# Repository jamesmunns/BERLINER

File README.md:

# BERLINER card/rack standard

BERLINER (BERLINER Euro Rack-Like Is Not Euro Rack) is an informal standard for USB and microcontroller oriented cards, using the eurorack form factor (but not the same power supply).

## The "standard"

Most of the "standard" here is the connector used on the boards. It's a 0.1" pitch 2x6 IDC connector. The picture above is taken looking at the BACK of the board.

The pins are:

| Use           | Pin   | Pin | Use             |
| :--           | :--   | --: | --:             |
| +20v power    | 1     |   2 |          Ground |
| +20v power    | 3     |   4 |          Ground |
| +5v0 power    | 5     |   6 |          Ground |
| +5v0 power    | 7     |   8 |          Ground |
| USB FS/HS D+  | 9     |  10 |    USB FS/HS D- |
| Ground        | 11    |  12 |          Common |

### "+20v power"

This is intended to be supplied by USB-PD, so it should be expected this rail can be any voltage 5v0 to 20v0 max. This rail is expected to have more wattage available than the +5v0 power rail. You may need a variable input DC/DC that can handle this.

### "+5v0 power"

This is a 5-volt-ish rail. Probably something in the tolerance of regular USB 5v, so +/- 0.25v. You can use this exclusively, but current may be shared with many other boards. If you need to do something high current, do it from the +20v power rail.

### "USB FS/HS D+/D-"

This is the normal differential pair used by USB Full Speed or USB High Speed.

### "Common"

This isn't super well defined, but it is intended as a low frequency, open-drain, interface, usable for clock sync or trigger. TBD who provides the pullup, maybe all boards on the order of 10k-50k (i.e. internal MCU pullups).

## `cards/` folder

These are board designs that are compatible with this "standard". They are intended to be mounted using the [Eurorack] device conventions, meaning a 128.5mm tall board, with M3 screws.

Some boards will have separate "face plates" or "covers" and "logic boards". In this case, the cover will be the full 128.5mm tall, and the logic board will often be a bit shorter (typ: 106.0mm), as it needs clearance to "drop into" the frame.

In these cases, covers will be mounted to the face plate either using hardware that is present (switches, dials), M3 headers, or some other mechanical means (outside the scope of this standard).

Feel free to open a PR with any designs you would like to share. KICAD designs preferred.

## `hubs/` folder

Since the cards don't take standard USB cables as input, it is generally necessary to have another PCBA that acts as an adapter. These have three main responsibilities:

1. Provide power to all boards, including the 20v0 rail and 5v0 rail
2. Provide data to all boards, often acting as a USB Hub
3. Provide 12-pin headers to connect to the cards, using an IDC ribbon cable

There are many options for chips that do this, but the CH334F (4 port USB hub) and CH224K (USB-PD negotiation) are used in some designs, and are available at reasonable prices.

Hubs can be present in two main forms:

1. As a "card", where the data and power ports face the front. See `hubs/usb-demo-4` for an example hub in this form factor.
2. As a "backplane", mounted somewhere inside the case, with connectors mounted somewhere on the case. See `hubs/backplane` for an example hub in this form factor, designed to fit the Sinusoda CAN eurorack case.

## License

idk something like cc-by-sa-nc?

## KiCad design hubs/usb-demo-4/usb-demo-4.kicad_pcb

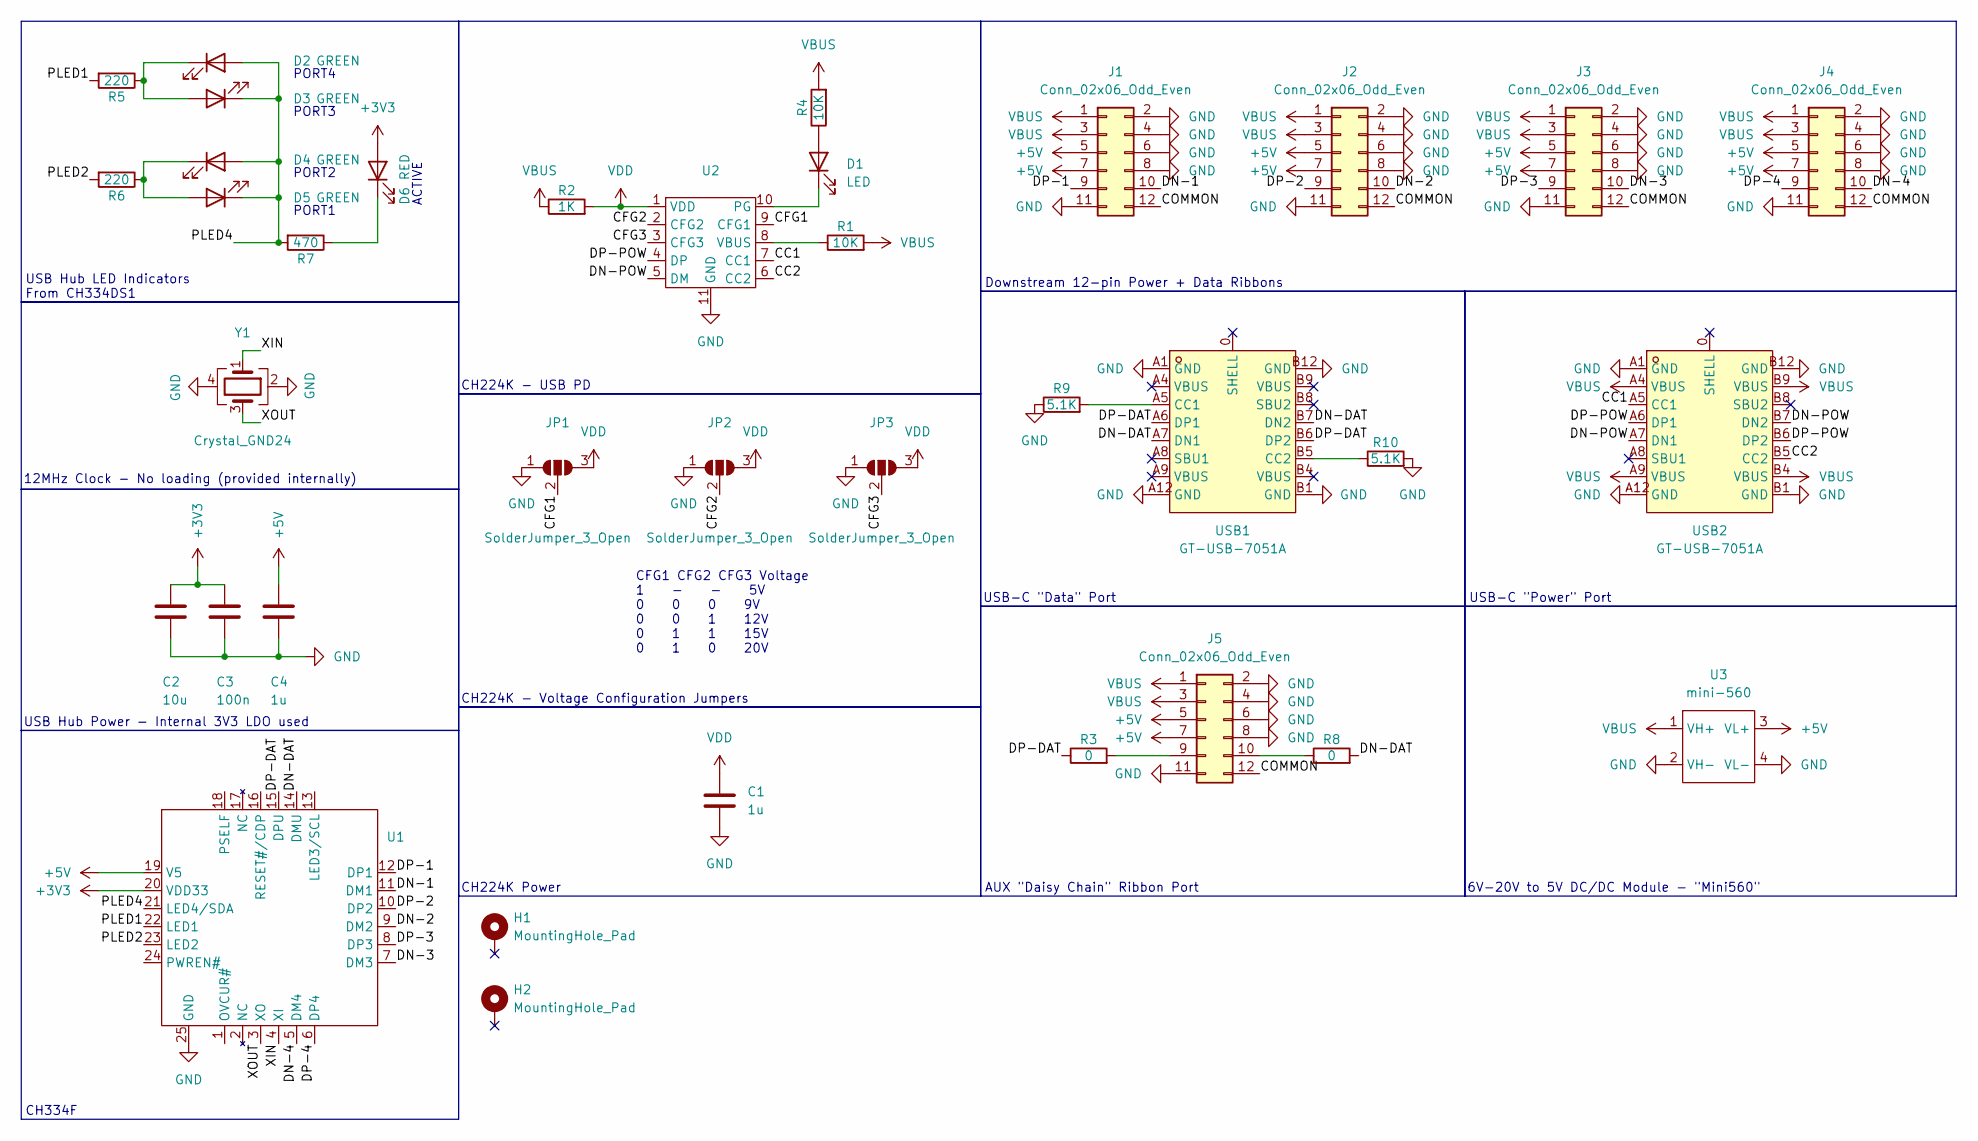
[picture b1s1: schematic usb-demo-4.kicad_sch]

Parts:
C1, C4: 1u; C_0603_1608Metric
C2: 10u; C_0603_1608Metric
C3: 100n; C_0603_1608Metric
D1: LED; D_0603_1608Metric
D2, D3, D4, D5: GREEN; D_0603_1608Metric
D6: RED; D_0603_1608Metric
H1, H2: MountingHole_Pad; MountingHole_3.2mm_M3_Pad_Via
J1, J2, J3, J4, J5: Conn_02x06_Odd_Even; PinHeader_2x06_P2.54mm_Vertical
JP1, JP2, JP3: SolderJumper_3_Open; SolderJumper-3_P2.0mm_Open_TrianglePad1.0x1.5mm
R1, R4: 10K; R_0603_1608Metric
R2: 1K; R_0603_1608Metric
R3, R8: 0; R_0603_1608Metric
R5, R6: 220; R_0603_1608Metric
R7: 470; R_0603_1608Metric
R9, R10: 5.1K; R_0603_1608Metric
U1: QFN-24-1EP_4x4mm_P0.5mm_EP2.7x2.7mm_ThermalVias
U2: ESSOP-10_L4.9-W3.9-P1.0-LS6.0-TL-EP
U3: mini-560; mini-560-smd
USB1, USB2: GT-USB-7051A; USB-C-SMD_GT-USB-7051A; LCSC Part C2843970
Y1: Crystal_GND24; Crystal_SMD_3225-4Pin_3.2x2.5mm

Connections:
+3V3: C2.1, C3.1, D6.2 (A), U1.20 (VDD33)
+5V: C4.1, J1.5, J1.7, J2.5, J2.7, J3.5, J3.7, J4.5, J4.7, J5.5, J5.7, U1.19 (V5), U3.3 (VL+)
/CC1: U2.7 (CC1), USB2.A5 (CC1)
/CC2: U2.6 (CC2), USB2.B5 (CC2)
/CFG1: JP1.2 (C), U2.9 (CFG1)
/CFG2: JP2.2 (C), U2.2 (CFG2)
/CFG3: JP3.2 (C), U2.3 (CFG3)
/COMMON: J1.12, J2.12, J3.12, J4.12, J5.12
/DN-1: J1.10, U1.11 (DM1)
/DN-2: J2.10, U1.9 (DM2)
/DN-3: J3.10, U1.7 (DM3)
/DN-4: J4.10, U1.5 (DM4)
/DN-DAT: R8.2, U1.14 (DMU), USB1.A7 (DN1), USB1.B7 (DN2)
/DN-POW: U2.5 (DM), USB2.A7 (DN1), USB2.B7 (DN2)
/DP-1: J1.9, U1.12 (DP1)
/DP-2: J2.9, U1.10 (DP2)
/DP-3: J3.9, U1.8 (DP3)
/DP-4: J4.9, U1.6 (DP4)
/DP-DAT: R3.1, U1.15 (DPU), USB1.A6 (DP1), USB1.B6 (DP2)
/DP-POW: U2.4 (DP), USB2.A6 (DP1), USB2.B6 (DP2)
/PLED1: R5.2, U1.22 (LED1)
/PLED2: R6.2, U1.23 (LED2)
/PLED4: D2.2 (A), D3.1 (K), D4.2 (A), D5.1 (K), R7.2, U1.21 (LED4/SDA)
/XIN: U1.4 (XI), Y1.1
/XOUT: U1.3 (XO), Y1.3
GND: C1.2, C2.2, C3.2, C4.2, J1.2, J1.4, J1.6, J1.8, J1.11, J2.2, J2.4, J2.6, J2.8, J2.11, J3.2, J3.4, J3.6, J3.8, J3.11, J4.2, J4.4, J4.6, J4.8, J4.11, J5.2, J5.4, J5.6, J5.8, J5.11, JP1.1 (A), JP2.1 (A), JP3.1 (A), R9.1, R10.2, U1.25 (GND), U2.11 (GND), U3.2 (VH-), U3.4 (VL-), USB1.A1 (GND), USB1.A12 (GND), USB1.B1 (GND), USB1.B12 (GND), USB2.A1 (GND), USB2.A12 (GND), USB2.B1 (GND), USB2.B12 (GND), Y1.2, Y1.4
unnamed: D1.2 (A), R4.1
unnamed: D1.1 (K), U2.10 (PG)
unnamed: D2.1 (K), D3.2 (A), R5.1
unnamed: D4.1 (K), D5.2 (A), R6.1
unnamed: D6.1 (K), R7.1
unnamed: J5.9, R3.2
unnamed: J5.10, R8.1
unnamed: R1.1, U2.8 (VBUS)
unnamed: R9.2, USB1.A5 (CC1)
unnamed: R10.1, USB1.B5 (CC2)
VBUS: J1.1, J1.3, J2.1, J2.3, J3.1, J3.3, J4.1, J4.3, J5.1, J5.3, R1.2, R2.1, R4.2, U3.1 (VH+), USB2.A4 (VBUS), USB2.A9 (VBUS), USB2.B4 (VBUS), USB2.B9 (VBUS)
VDD: C1.1, JP1.3 (B), JP2.3 (B), JP3.3 (B), R2.2, U2.1 (VDD)

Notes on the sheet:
CH224K - Voltage Configuration Jumpers
USB-C "Data" Port
AUX "Daisy Chain" Ribbon Port
USB Hub LED Indicators From CH334DS1
CFG1 CFG2 CFG3 Voltage 1 - - 5V 0 0 0 9V 0 0 1 12V 0 1 1 15V 0 1 0 20V
Downstream 12-pin Power + Data Ribbons
USB-C "Power" Port
PORT1
PORT2
ACTIVE
PORT4
CH334F
12MHz Clock - No loading (provided internally)
CH224K Power
6V-20V to 5V DC/DC Module - "Mini560"
USB Hub Power - Internal 3V3 LDO used
PORT3
CH224K - USB PD

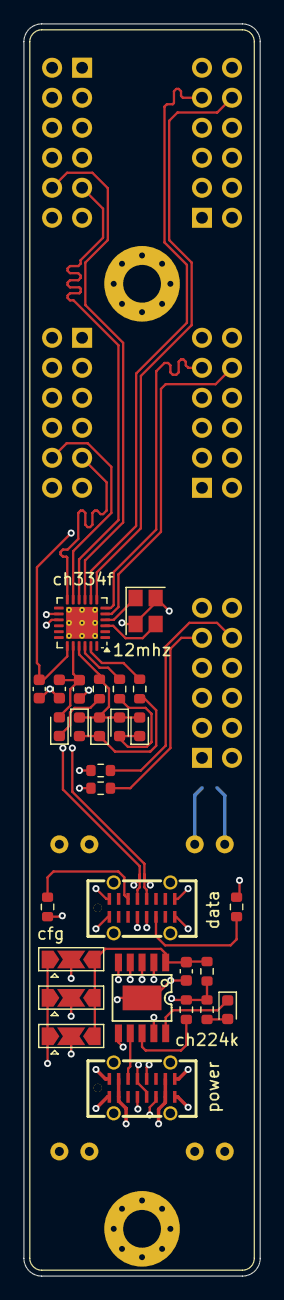
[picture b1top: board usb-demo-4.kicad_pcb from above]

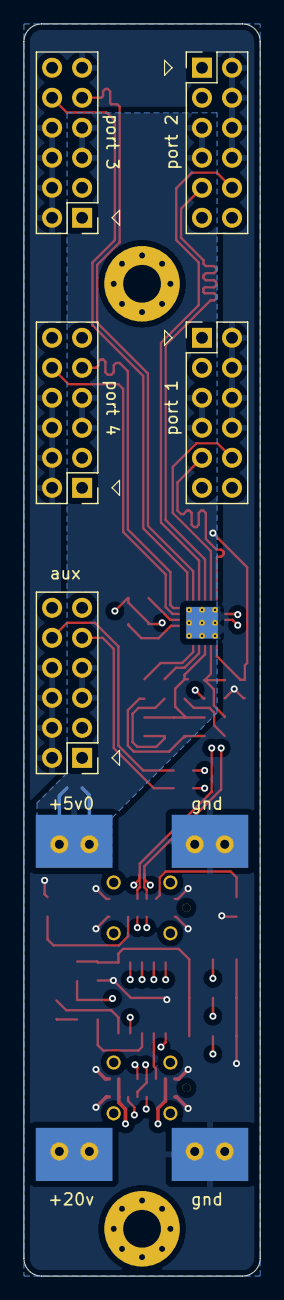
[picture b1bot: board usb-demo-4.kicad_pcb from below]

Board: 4 copper layers, 20.0 x 106.0 mm, 36 parts (6 on the bottom side), 38 nets.

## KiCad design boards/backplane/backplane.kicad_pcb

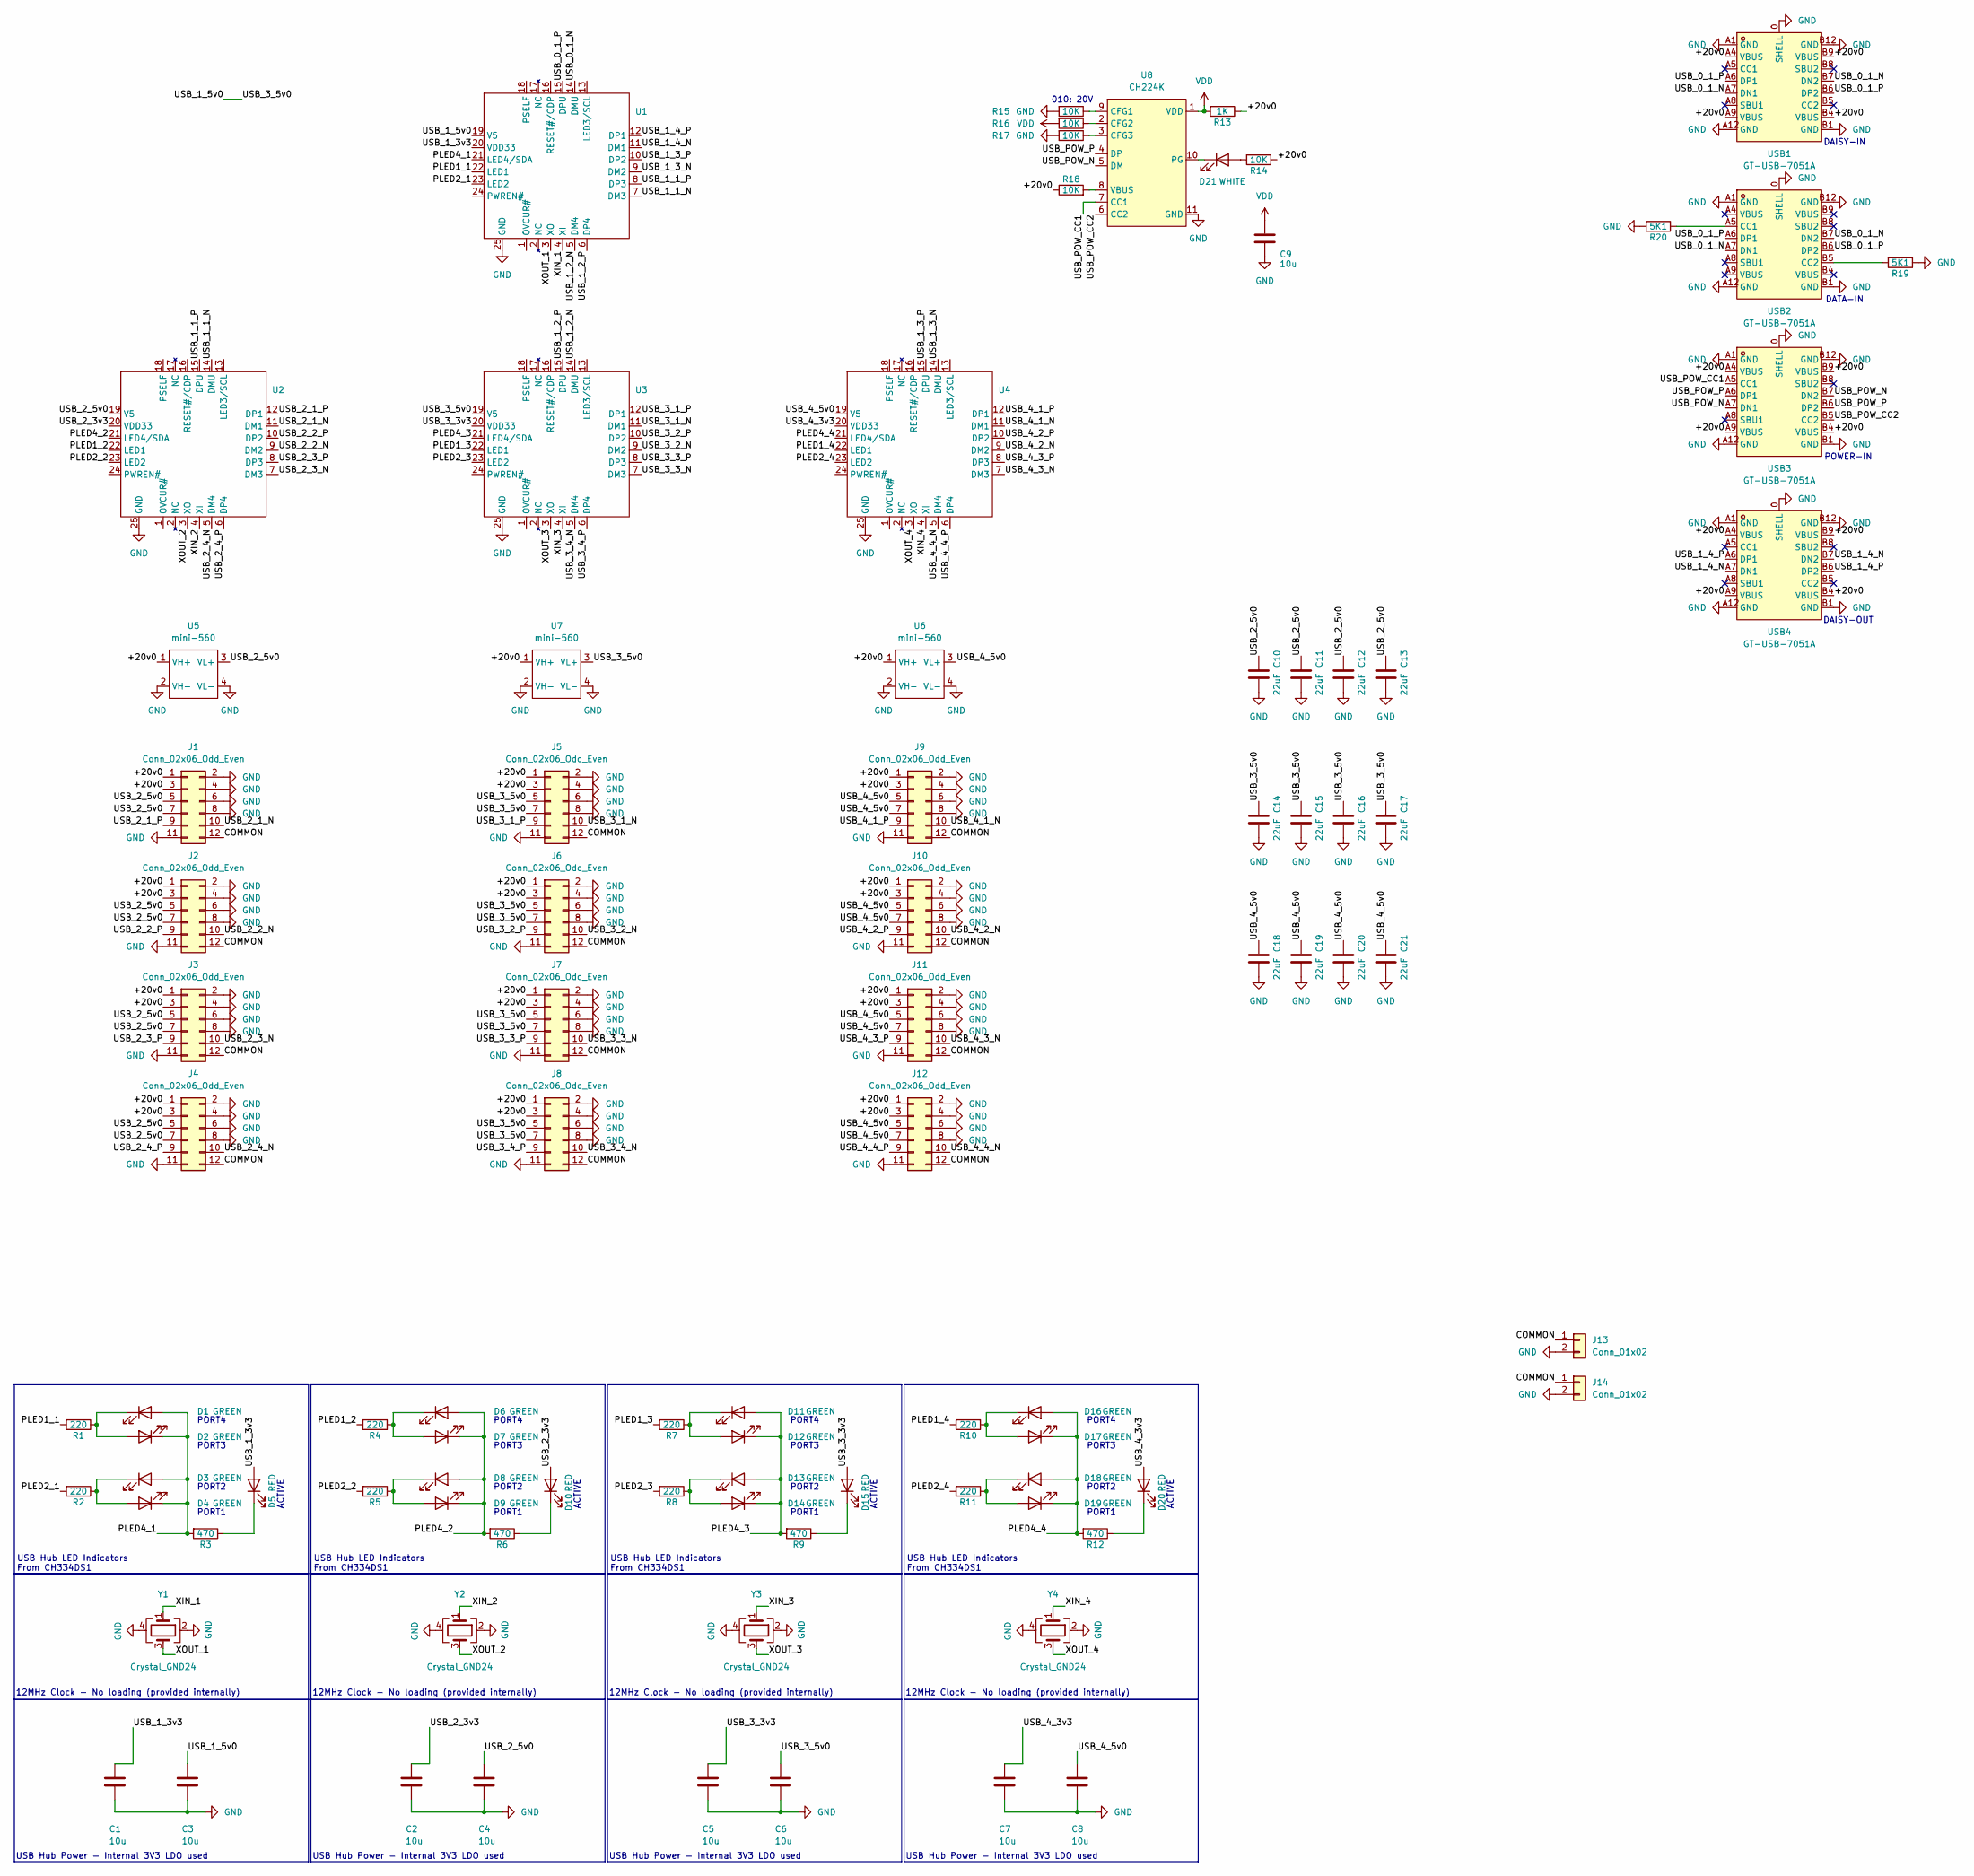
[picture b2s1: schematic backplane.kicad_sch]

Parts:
C1, C2, C3, C4, C5, C6, C7, C8, C9: 10u; C_0603_1608Metric
C10, C11, C12, C13, C14, C15, C16, C17, C18, C19, C20, C21: 22uF; C_0805_2012Metric
D1, D2, D3, D4, D6, D7, D8, D9, D11, D12, D13, D14, D16, D17, D18, D19: GREEN; D_0603_1608Metric
D5, D10, D15, D20: RED; D_0603_1608Metric
D21: WHITE; D_0603_1608Metric
J1, J2, J3, J4, J5, J6, J7, J8, J9, J10, J11, J12: Conn_02x06_Odd_Even; IDC-Header_2x06_P2.54mm_Vertical
J13, J14: Conn_01x02; PinHeader_1x02_P2.54mm_Vertical
R1, R2, R4, R5, R7, R8, R10, R11: 220; R_0603_1608Metric
R3, R6, R9, R12: 470; R_0603_1608Metric
R13: 1K; R_0603_1608Metric
R14, R15, R16, R17, R18: 10K; R_0603_1608Metric
R19, R20: 5K1; R_0603_1608Metric
U1, U2, U3, U4: QFN-24-1EP_4x4mm_P0.5mm_EP2.7x2.7mm_ThermalVias
U5, U6, U7: mini-560; mini-560-smd
U8: CH224K; ESSOP-10_L4.9-W3.9-P1.0-LS6.0-TL-EP; LCSC Part C970725
USB1, USB2, USB3, USB4: GT-USB-7051A; USB-C-SMD_GT-USB-7051A; LCSC Part C2843970
Y1, Y2, Y3, Y4: Crystal_GND24; Crystal_SMD_3225-4Pin_3.2x2.5mm

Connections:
/+20v0: J1.1, J1.3, J2.1, J2.3, J3.1, J3.3, J4.1, J4.3, J5.1, J5.3, J6.1, J6.3, J7.1, J7.3, J8.1, J8.3, J9.1, J9.3, J10.1, J10.3, J11.1, J11.3, J12.1, J12.3, R13.1, R14.1, R18.1, U5.1 (VH+), U6.1 (VH+), U7.1 (VH+), USB1.A4 (VBUS), USB1.A9 (VBUS), USB1.B4 (VBUS), USB1.B9 (VBUS), USB3.A4 (VBUS), USB3.A9 (VBUS), USB3.B4 (VBUS), USB3.B9 (VBUS), USB4.A4 (VBUS), USB4.A9 (VBUS), USB4.B4 (VBUS), USB4.B9 (VBUS)
/COMMON: J1.12, J2.12, J3.12, J4.12, J5.12, J6.12, J7.12, J8.12, J9.12, J10.12, J11.12, J12.12, J13.1, J14.1
/PLED1_1: R1.2, U1.22 (LED1)
/PLED1_2: R4.2, U2.22 (LED1)
/PLED1_3: R7.2, U3.22 (LED1)
/PLED1_4: R10.2, U4.22 (LED1)
/PLED2_1: R2.2, U1.23 (LED2)
/PLED2_2: R5.2, U2.23 (LED2)
/PLED2_3: R8.2, U3.23 (LED2)
/PLED2_4: R11.2, U4.23 (LED2)
/PLED4_1: D1.2 (A), D2.1 (K), D3.2 (A), D4.1 (K), R3.2, U1.21 (LED4/SDA)
/PLED4_2: D6.2 (A), D7.1 (K), D8.2 (A), D9.1 (K), R6.2, U2.21 (LED4/SDA)
/PLED4_3: D11.2 (A), D12.1 (K), D13.2 (A), D14.1 (K), R9.2, U3.21 (LED4/SDA)
/PLED4_4: D16.2 (A), D17.1 (K), D18.2 (A), D19.1 (K), R12.2, U4.21 (LED4/SDA)
/USB_0_1_N: U1.14 (DMU), USB1.A7 (DN1), USB1.B7 (DN2), USB2.A7 (DN1), USB2.B7 (DN2)
/USB_0_1_P: U1.15 (DPU), USB1.A6 (DP1), USB1.B6 (DP2), USB2.A6 (DP1), USB2.B6 (DP2)
/USB_1_1_N: U1.7 (DM3), U2.14 (DMU)
/USB_1_1_P: U1.8 (DP3), U2.15 (DPU)
/USB_1_2_N: U1.5 (DM4), U3.14 (DMU)
/USB_1_2_P: U1.6 (DP4), U3.15 (DPU)
/USB_1_3_N: U1.9 (DM2), U4.14 (DMU)
/USB_1_3_P: U1.10 (DP2), U4.15 (DPU)
/USB_1_3v3: C1.1, D5.2 (A), U1.20 (VDD33)
/USB_1_4_N: U1.11 (DM1), USB4.A7 (DN1), USB4.B7 (DN2)
/USB_1_4_P: U1.12 (DP1), USB4.A6 (DP1), USB4.B6 (DP2)
/USB_1_5v0: C3.1, C6.1, C14.1, C15.1, C16.1, C17.1, J5.5, J5.7, J6.5, J6.7, J7.5, J7.7, J8.5, J8.7, U1.19 (V5), U3.19 (V5), U7.3 (VL+)
/USB_2_1_N: J1.10, U2.11 (DM1)
/USB_2_1_P: J1.9, U2.12 (DP1)
/USB_2_2_N: J2.10, U2.9 (DM2)
/USB_2_2_P: J2.9, U2.10 (DP2)
/USB_2_3_N: J3.10, U2.7 (DM3)
/USB_2_3_P: J3.9, U2.8 (DP3)
/USB_2_3v3: C2.1, D10.2 (A), U2.20 (VDD33)
/USB_2_4_N: J4.10, U2.5 (DM4)
/USB_2_4_P: J4.9, U2.6 (DP4)
/USB_2_5v0: C4.1, C10.1, C11.1, C12.1, C13.1, J1.5, J1.7, J2.5, J2.7, J3.5, J3.7, J4.5, J4.7, U2.19 (V5), U5.3 (VL+)
/USB_3_1_N: J5.10, U3.11 (DM1)
/USB_3_1_P: J5.9, U3.12 (DP1)
/USB_3_2_N: J6.10, U3.9 (DM2)
/USB_3_2_P: J6.9, U3.10 (DP2)
/USB_3_3_N: J7.10, U3.7 (DM3)
/USB_3_3_P: J7.9, U3.8 (DP3)
/USB_3_3v3: C5.1, D15.2 (A), U3.20 (VDD33)
/USB_3_4_N: J8.10, U3.5 (DM4)
/USB_3_4_P: J8.9, U3.6 (DP4)
/USB_4_1_N: J9.10, U4.11 (DM1)
/USB_4_1_P: J9.9, U4.12 (DP1)
/USB_4_2_N: J10.10, U4.9 (DM2)
/USB_4_2_P: J10.9, U4.10 (DP2)
/USB_4_3_N: J11.10, U4.7 (DM3)
/USB_4_3_P: J11.9, U4.8 (DP3)
/USB_4_3v3: C7.1, D20.2 (A), U4.20 (VDD33)
/USB_4_4_N: J12.10, U4.5 (DM4)
/USB_4_4_P: J12.9, U4.6 (DP4)
/USB_4_5v0: C8.1, C18.1, C19.1, C20.1, C21.1, J9.5, J9.7, J10.5, J10.7, J11.5, J11.7, J12.5, J12.7, U4.19 (V5), U6.3 (VL+)
/USB_POW_CC1: U8.7 (CC1), USB3.A5 (CC1)
/USB_POW_CC2: U8.6 (CC2), USB3.B5 (CC2)
/USB_POW_N: U8.5 (DM), USB3.A7 (DN1), USB3.B7 (DN2)
/USB_POW_P: U8.4 (DP), USB3.A6 (DP1), USB3.B6 (DP2)
/XIN_1: U1.4 (XI), Y1.1
/XIN_2: U2.4 (XI), Y2.1
/XIN_3: U3.4 (XI), Y3.1
/XIN_4: U4.4 (XI), Y4.1
/XOUT_1: U1.3 (XO), Y1.3
/XOUT_2: U2.3 (XO), Y2.3
/XOUT_3: U3.3 (XO), Y3.3
/XOUT_4: U4.3 (XO), Y4.3
GND: C1.2, C2.2, C3.2, C4.2, C5.2, C6.2, C7.2, C8.2, C9.2, C10.2, C11.2, C12.2, C13.2, C14.2, C15.2, C16.2, C17.2, C18.2, C19.2, C20.2, C21.2, J1.2, J1.4, J1.6, J1.8, J1.11, J2.2, J2.4, J2.6, J2.8, J2.11, J3.2, J3.4, J3.6, J3.8, J3.11, J4.2, J4.4, J4.6, J4.8, J4.11, J5.2, J5.4, J5.6, J5.8, J5.11, J6.2, J6.4, J6.6, J6.8, J6.11, J7.2, J7.4, J7.6, J7.8, J7.11, J8.2, J8.4, J8.6, J8.8, J8.11, J9.2, J9.4, J9.6, J9.8, J9.11, J10.2, J10.4, J10.6, J10.8, J10.11, J11.2, J11.4, J11.6, J11.8, J11.11, J12.2, J12.4, J12.6, J12.8, J12.11, J13.2, J14.2, R15.2, R17.2, R19.1, R20.2, U1.25 (GND), U2.25 (GND), U3.25 (GND), U4.25 (GND), U5.2 (VH-), U5.4 (VL-), U6.2 (VH-), U6.4 (VL-), U7.2 (VH-), U7.4 (VL-), U8.11 (GND), USB1.0 (SHELL), USB1.A1 (GND), USB1.A12 (GND), USB1.B1 (GND), USB1.B12 (GND), USB2.0 (SHELL), USB2.A1 (GND), USB2.A12 (GND), USB2.B1 (GND), USB2.B12 (GND), USB3.0 (SHELL), USB3.A1 (GND), USB3.A12 (GND), USB3.B1 (GND), USB3.B12 (GND), USB4.0 (SHELL), USB4.A1 (GND), USB4.A12 (GND), USB4.B1 (GND), USB4.B12 (GND), Y1.2, Y1.4, Y2.2, Y2.4, Y3.2, Y3.4, Y4.2, Y4.4
unnamed: D1.1 (K), D2.2 (A), R1.1
unnamed: D3.1 (K), D4.2 (A), R2.1
unnamed: D5.1 (K), R3.1
unnamed: D6.1 (K), D7.2 (A), R4.1
unnamed: D8.1 (K), D9.2 (A), R5.1
unnamed: D10.1 (K), R6.1
unnamed: D11.1 (K), D12.2 (A), R7.1
unnamed: D13.1 (K), D14.2 (A), R8.1
unnamed: D15.1 (K), R9.1
unnamed: D16.1 (K), D17.2 (A), R10.1
unnamed: D18.1 (K), D19.2 (A), R11.1
unnamed: D20.1 (K), R12.1
unnamed: D21.2 (A), R14.2
unnamed: D21.1 (K), U8.10 (PG)
unnamed: R15.1, U8.9 (CFG1)
unnamed: R16.1, U8.2 (CFG2)
unnamed: R17.1, U8.3 (CFG3)
unnamed: R18.2, U8.8 (VBUS)
unnamed: R20.1, USB2.A5 (CC1)
unnamed: R19.2, USB2.B5 (CC2)
VDD: C9.1, R13.2, R16.2, U8.1 (VDD)

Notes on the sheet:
DAISY-OUT
PORT3
USB Hub Power - Internal 3V3 LDO used
USB Hub LED Indicators From CH334DS1
PORT4
DATA-IN
12MHz Clock - No loading (provided internally)
ACTIVE
PORT2
PORT1
010: 20V
POWER-IN
DAISY-IN

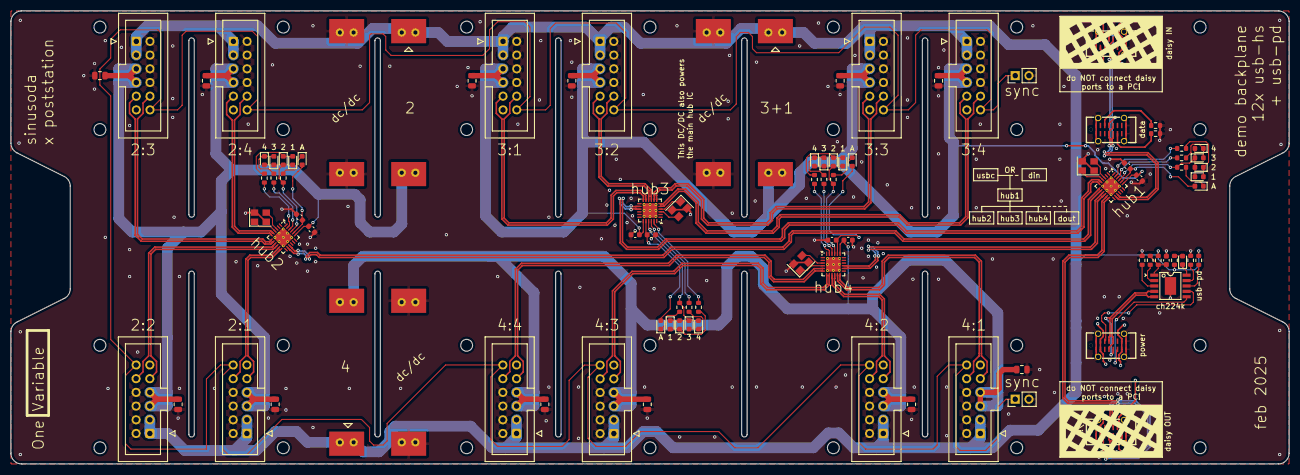
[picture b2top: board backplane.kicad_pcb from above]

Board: 4 copper layers, 237.0 x 84.0 mm, 92 parts (0 on the bottom side), 89 nets.

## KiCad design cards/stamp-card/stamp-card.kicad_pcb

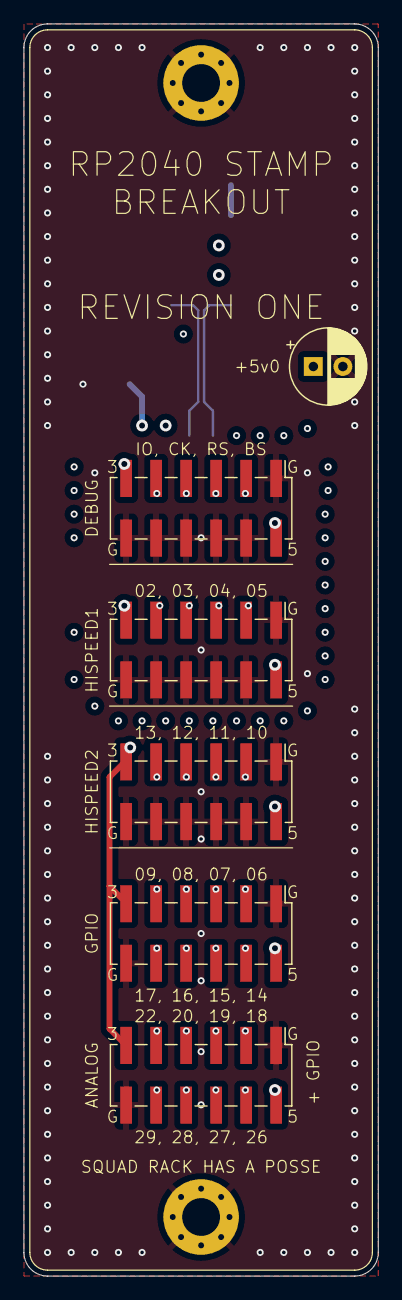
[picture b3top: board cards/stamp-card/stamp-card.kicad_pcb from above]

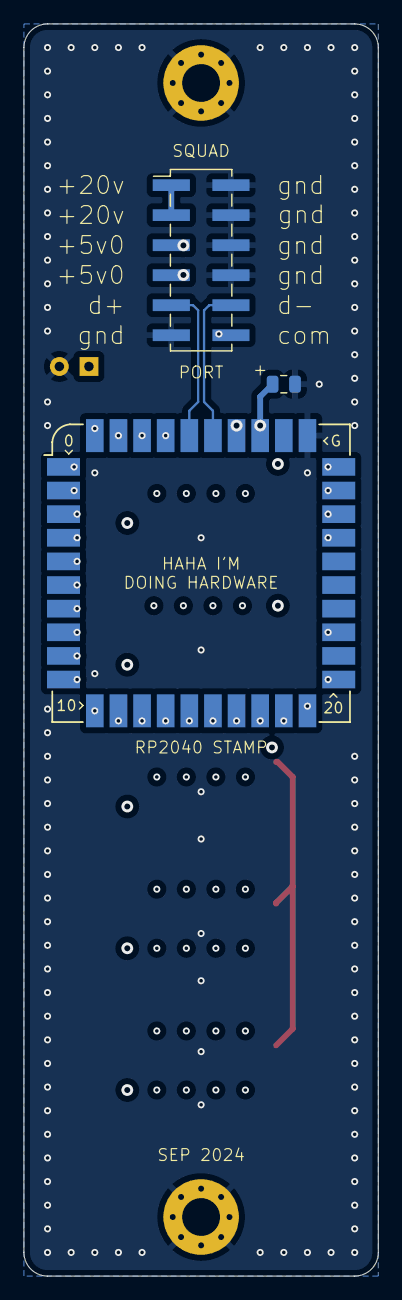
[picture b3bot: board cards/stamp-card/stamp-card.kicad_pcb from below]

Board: 4 copper layers, 30.0 x 106.0 mm, 11 parts (3 on the bottom side), 35 nets.

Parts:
C1: C; C_0805_2012Metric
C2: C; CP_Radial_D6.3mm_P2.50mm
H1, H2: MountingHole_Pad; MountingHole_3.2mm_M3_Pad_Via
J1, J2, J3, J4, J5, J6: Conn_02x06_Odd_Even; PinHeader_2x06_P2.54mm_Vertical_SMD
U1: RP2040_Stamp; RP2xxx_Stamp_SMD

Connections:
+3.3V: J2.11, J3.11, J4.11, J5.11, J6.11, U1.34 (3.3V)
+5V: C1.1, C2.1, J1.5, J1.7, J2.2, J3.2, J4.2, J5.2, J6.2, U1.33 (5V)
/BOOTSEL: J6.3, U1.40 (BOOTSEL)
/COMMON: J1.12, U1.1 (GPIO0), U1.2 (GPIO1)
/DN: J1.10, U1.35 (USB_D-)
/DP: J1.9, U1.36 (USB_D+)
/G02: J2.9, U1.3 (GPIO2)
/G03: J2.7, U1.4 (GPIO3)
/G04: J2.5, U1.5 (GPIO4)
/G05: J2.3, U1.6 (GPIO5)
/G06: J4.3, U1.7 (GPIO6)
/G07: J4.5, U1.8 (GPIO7)
/G08: J4.7, U1.9 (GPIO8)
/G09: J4.9, U1.10 (GPIO9)
/G10: J3.3, U1.11 (GPIO10)
/G11: J3.5, U1.12 (GPIO11)
/G12: J3.7, U1.13 (GPIO12)
/G13: J3.9, U1.14 (GPIO13)
/G14: J4.4, U1.15 (GPIO14)
/G15: J4.6, U1.16 (GPIO15)
/G16: J4.8, U1.17 (GPIO16)
/G17: J4.10, U1.18 (GPIO17)
/G18: J5.3, U1.19 (GPIO18)
/G19: J5.5, U1.20 (GPIO19)
/G20: J5.7, U1.21 (GPIO20)
/G22: J5.9, U1.23 (GPIO22)
/G26: J5.4, U1.27 (GPIO26)
/G27: J5.6, U1.28 (GPIO27)
/G28: J5.8, U1.29 (GPIO28)
/G29: J5.10, U1.30 (GPIO29)
/SWCLK: J6.7, U1.38 (SWCLK)
/SWDIO: J6.9, U1.37 (SWDIO)
/nRESET: J6.5, U1.39 (~RESET)
GND: C1.2, C2.2, H1.1, H2.1, J1.2, J1.4, J1.6, J1.8, J1.11, J2.1, J2.4, J2.6, J2.8, J2.10, J2.12, J3.1, J3.4, J3.6, J3.8, J3.10, J3.12, J4.1, J4.12, J5.1, J5.12, J6.1, J6.4, J6.6, J6.8, J6.10, J6.12, U1.31 (GND)
VBUS: J1.1, J1.3

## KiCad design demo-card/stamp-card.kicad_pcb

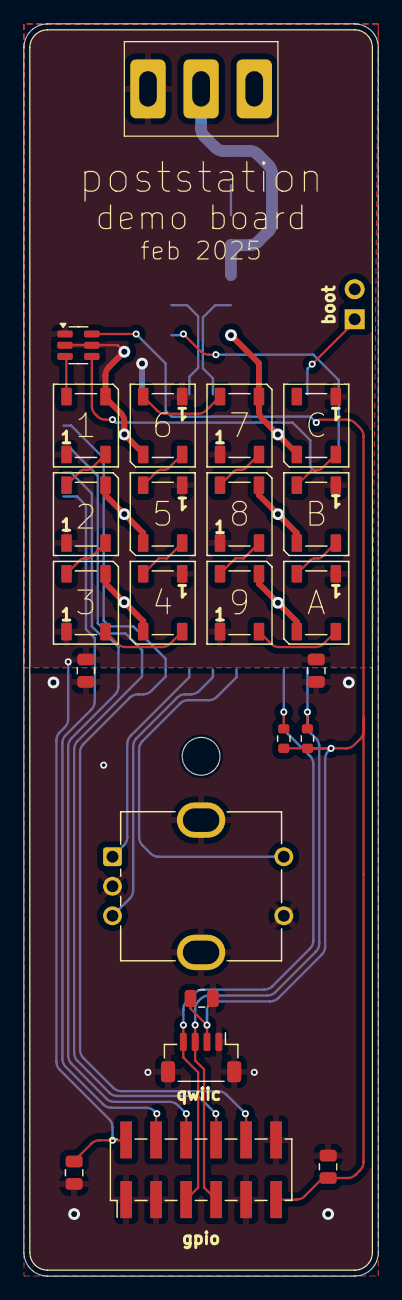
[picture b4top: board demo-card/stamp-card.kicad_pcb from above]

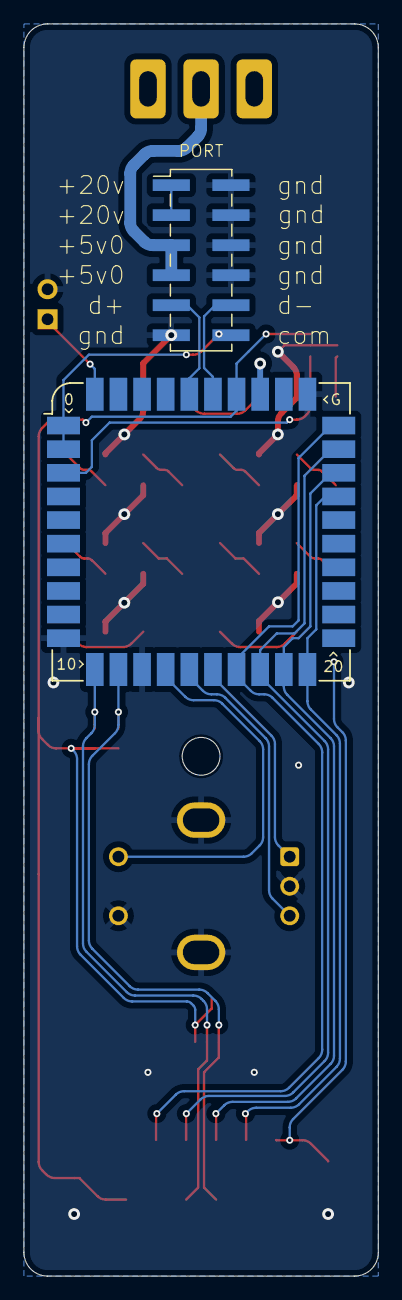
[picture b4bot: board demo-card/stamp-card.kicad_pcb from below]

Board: 2 copper layers, 30.0 x 106.0 mm, 28 parts (2 on the bottom side), 31 nets.

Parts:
C1, C2, C3, C4, C5: C; C_0805_2012Metric
D1, D2, D3, D4, D5, D6, D7, D8, D9, D10, D11, D12: WS2812B; LED_WS2812B_PLCC4_5.0x5.0mm_P3.2mm
H1: MountingHole; MountingHole_3.2mm_M3
J1, J3: Conn_02x06_Odd_Even; PinHeader_2x06_P2.54mm_Vertical_SMD
J2: Conn_01x04_MountingPin; JST_SH_BM04B-SRSS-TB_1x04-1MP_P1.00mm_Vertical
J4: Conn_01x03; panel-switch
J5: Conn_01x02; PinHeader_1x02_P2.54mm_Vertical
R1, R2: 10k; R_0603_1608Metric
SW1: RotaryEncoder_Switch; RotaryEncoder_Bourns_Vertical_PEC12R-3x17F-Sxxxx
U1: RP2040_Stamp; RP2xxx_Stamp_SMD
U2: SN74LVC1T45DBV; SOT-23-6

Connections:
+3.3V: C3.1, C5.1, J2.2, J3.11, R1.1, R2.1, U1.34 (3.3V), U2.6 (VCCB)
+5V: J1.5, J1.7, J4.2
/+5v0-switched: C1.1, C2.1, C4.1, D1.1 (VDD), D2.1 (VDD), D3.1 (VDD), D4.1 (VDD), D5.1 (VDD), D6.1 (VDD), D7.1 (VDD), D8.1 (VDD), D9.1 (VDD), D10.1 (VDD), D11.1 (VDD), D12.1 (VDD), J3.2, J4.1, U1.33 (5V), U2.1 (VCCA)
/BOOTSEL: J5.1, U1.40 (BOOTSEL)
/COMMON: J1.12, U1.1 (GPIO0), U1.2 (GPIO1)
/DN: J1.10, U1.35 (USB_D-)
/DP: J1.9, U1.36 (USB_D+)
/G26: J3.4, U1.20 (GPIO19), U1.27 (GPIO26)
/G27: J3.6, U1.19 (GPIO18), U1.28 (GPIO27)
/G28: J3.8, U1.18 (GPIO17), U1.29 (GPIO28)
/G29: J3.10, U1.17 (GPIO16), U1.30 (GPIO29)
/SCL: J2.4, J3.5, R2.2, U1.12 (GPIO11)
/SDA: J2.3, J3.7, R1.2, U1.11 (GPIO10)
/rotary-a: SW1.A, U1.16 (GPIO15)
/rotary-b: SW1.B, U1.15 (GPIO14)
/rotary-switch: SW1.S1, U1.14 (GPIO13)
/smartled-3v: U1.3 (GPIO2), U2.4 (B)
/smartled-5v: D1.4 (DIN), U2.3 (A)
GND: C1.2, C2.2, C3.2, C4.2, C5.2, D1.3 (VSS), D2.3 (VSS), D3.3 (VSS), D4.3 (VSS), D5.3 (VSS), D6.3 (VSS), D7.3 (VSS), D8.3 (VSS), D9.3 (VSS), D10.3 (VSS), D11.3 (VSS), D12.3 (VSS), J1.2, J1.4, J1.6, J1.8, J1.11, J2.1, J2.MP (MountPin), J3.1, J3.3, J3.9, J3.12, J5.2, SW1.C, SW1.S2, SW1.SH, U1.10 (GPIO9), U1.13 (GPIO12), U1.31 (GND), U2.2 (GND), U2.5 (DIR)
unnamed: D1.2 (DOUT), D2.4 (DIN)
unnamed: D2.2 (DOUT), D3.4 (DIN)
unnamed: D3.2 (DOUT), D4.4 (DIN)
unnamed: D4.2 (DOUT), D5.4 (DIN)
unnamed: D5.2 (DOUT), D6.4 (DIN)
unnamed: D6.2 (DOUT), D7.4 (DIN)
unnamed: D7.2 (DOUT), D8.4 (DIN)
unnamed: D8.2 (DOUT), D9.4 (DIN)
unnamed: D9.2 (DOUT), D10.4 (DIN)
unnamed: D10.2 (DOUT), D11.4 (DIN)
unnamed: D11.2 (DOUT), D12.4 (DIN)
VBUS: J1.1, J1.3

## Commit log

2024-11-27 Initial (public) commit
2025-03-03 Add demo cards
2025-03-03 Add new boards, move to folder
2025-03-03 Add some docs
2025-03-04 Split up "hubs" and "cards"
2025-03-04 It has a name!
2025-04-18 Fix missing CC resistors on the usb-demo-4 data port
